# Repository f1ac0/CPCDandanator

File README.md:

# CPCDandanator
This project is a personal version of the famous "CPC Dandanator! Mini" by Dandare : http://www.dandare.es/Proyectos_Dandare/CPC_Dandanator%21_Mini.html .

Facts about this project :
- I wanted badly to try out "Sword of Ianna", so I built it on breadboard with the parts I had in stock :
- Flash ROM in DIP format,
- XC9572XL in VQ64 package (although Kicad files with VQ44 are also provided).

It ended on its own PCB with additional changes : 
- It can accommodate a card-edge connector or a pin header.
- I used a crystal-less CH340E to reduce BOM. WARNING: serial/USB communication does not work for me :( 

# Disclaimer
This is a hobbyist project, it comes with no warranty and no support. Also remember that the Amstrad machines are about 30 years old and may fail because of such hardware expansions.

The original "CPC Dandanator! Mini" is "a Public Domain project and all code/hardware/description is free to use with no restriction whatsoever" thanks to its author.

This version is not connected to Dandare, please don't bother him with issues you might have because of it.

If you find it useful and want to reward someone : reward the original author.

# BOM
- 1x XC9572XL CPLD
- 1x DIP SST39SF040, with socket
- 1x CH340E USB-serial converter + 1x micro USB connector
- 1x 3.3v LDO, either SPX3819M5-L-3-3 or XC6206P332MR
- 2x 1uF (or more) 0805 capacitors
- 5x 100nF 0805 capacitors
- 2x 10k 0805 resistor
- 1x 50 pins card-edge connector, or pin headers + cable to match your CPC

# Making it
Components are SMD, and have thin pin pitch. You need to know what you are doing.

Check for shorts at least between 5V, 3.3V, and GND traces before applying power !

The programming port does not need to be soldered since it needs to be programmed just once : you can just hold it in place during the few seconds required for programming.

XC9572XL code is generated and built into xsvf using Xilinx ISE 14.7 IDE then iMPACT. It requires to set "Logic optimization" to "Density". "Macrocell power setting" can be "Low" an "Slew rate" to "Slow". Original xsvf file provided by the author may work but I never tried it.

There are several methods to program the CPLD. I personally use xsvfduino : https://github.com/wschutzer/xsvfduino

CH340E and USB connector are optional if you do not plan to use USB. They dit not work for me anyway.

# Using it
This part is the same as the original device. Enjoy !

If you are a linux user like me, here is a tip to use the java application on modern systems without breaking the latest openjre provided by your distro :
- get oracle jre (for example from http://download.macromedia.com/pub/coldfusion/java/java8/8u271/jre/jre-8u271-linux-x64.tar.gz) and untar it
- start the app with ```~/jre1.8.0_271/bin/java -jar dandanator-cpc-2.3.jar```

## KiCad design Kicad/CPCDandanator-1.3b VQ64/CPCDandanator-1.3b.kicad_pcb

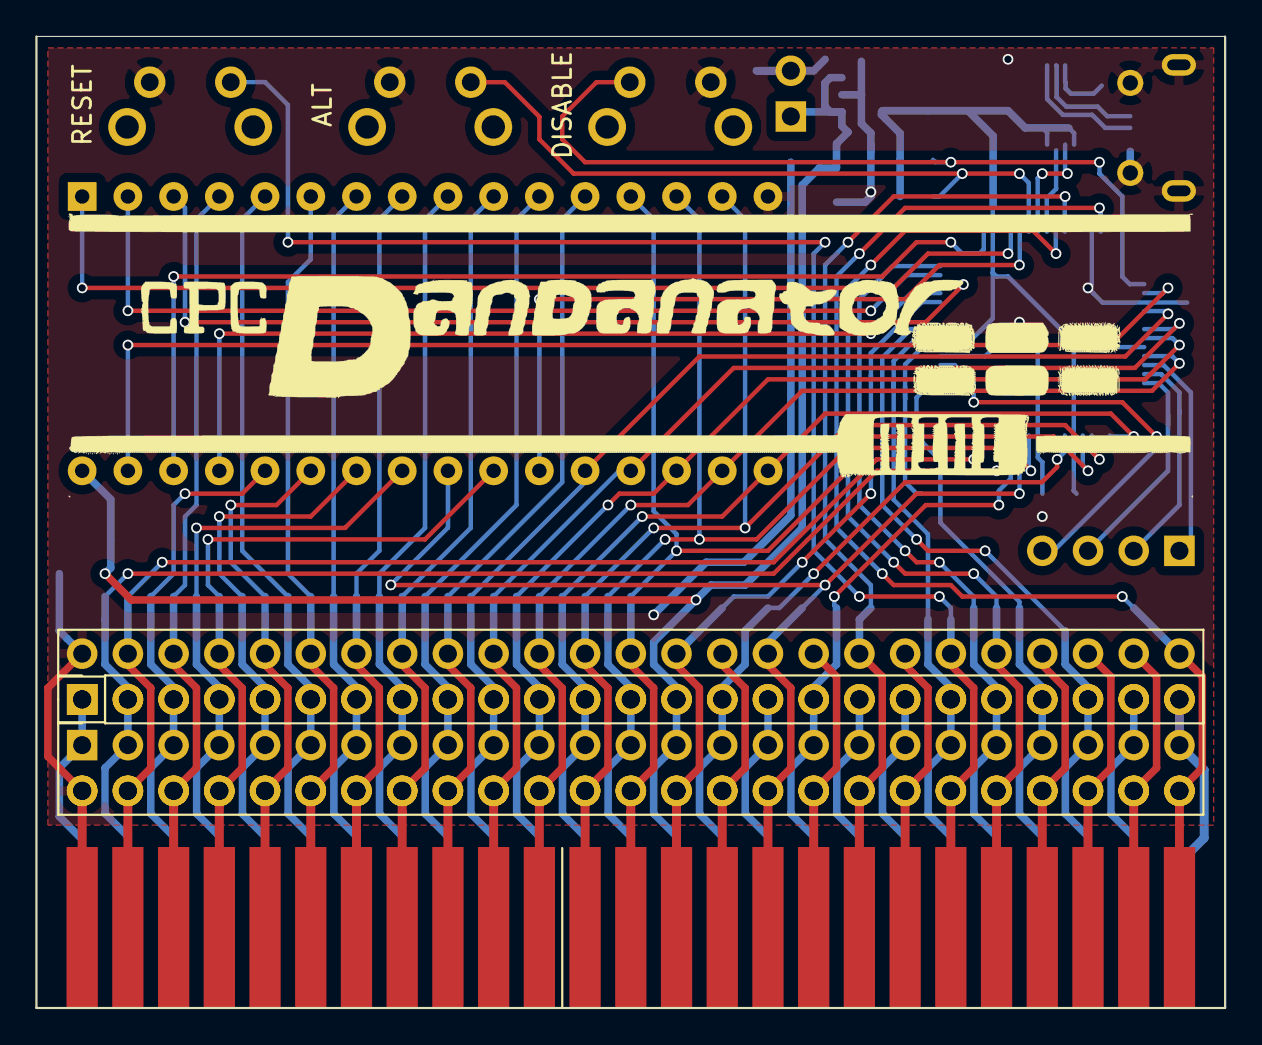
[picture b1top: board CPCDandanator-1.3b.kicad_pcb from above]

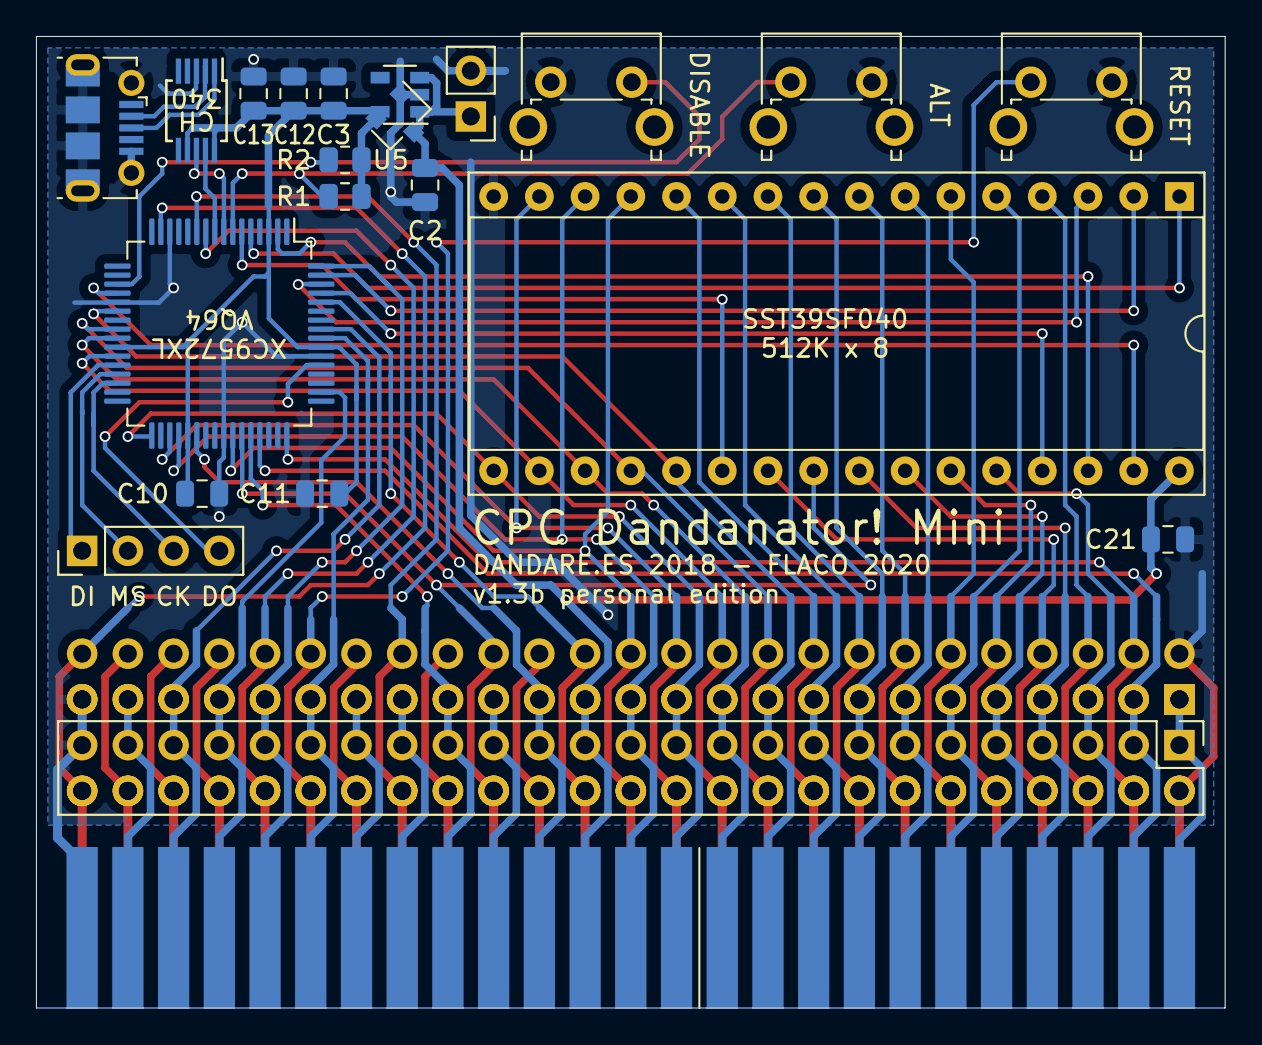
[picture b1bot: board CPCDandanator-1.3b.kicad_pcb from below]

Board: 2 copper layers, 66.0 x 54.0 mm, 25 parts (22 on the bottom side), 67 nets.

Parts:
C2, C3: 10uF; C_0805_2012Metric
C10, C11, C12, C13, C21: 100n; C_0805_2012Metric
FID1: Logo; PIC_Dandanator_FS_B
J1: TO CPC CARD EDGE; CPC_ExpansionSocket_2x25_P2.54mm_5mm
J2: TO CPC MX-4 ribbon; PinHeader_2x25_P2.54mm_Vertical
J3: POWER; PinHeader_1x02_P2.54mm_Vertical
J4: CPLD_JTAG; PinHeader_1x04_P2.54mm_Vertical
J5: USB_B_Micro; USB_Micro-B_Molex-105017-0001
J8: FROM EXPANSION; BUS_Amstrad_CPC_Expansion_2x25_2.54mm
J9: FROM EXPANSION; PinHeader_2x25_P2.54mm_Vertical
R1, R2: 10k; R_0805_2012Metric
SW1: RESET; SW_Tactile_SPST_Angled_PTS645Vx39-2LFS
SW3: ALTERNATE; SW_Tactile_SPST_Angled_PTS645Vx39-2LFS
SW4: DISABLE; SW_Tactile_SPST_Angled_PTS645Vx39-2LFS
U1: XC9572XL-VQ64; TQFP-64_10x10mm_P0.5mm
U3: 29C040; DIP-32_W15.24mm_Socket
U5: SPX3819M5-L-3-3; SOT-23-5
U12: CH340E; MSOP-10_3x3mm_P0.5mm
U15: XC6206PxxxMR; SOT-23

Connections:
+3V3: C3.1, C10.1, C11.1, C12.1, C13.1, R1.1, R2.1, U1.3, U1.26, U1.37, U1.55, U5.5, U12.7, U12.10, U15.2
+5V: C2.1, C21.1, J1.27, J2.27, J3.1, J8.27, J9.27, U3.32, U5.1, U5.3, U15.3
/A0: J1.18, J2.18, J8.18, J9.18, U3.12
/A1: J1.17, J2.17, J8.17, J9.17, U3.11
/A2: J1.16, J2.16, J8.16, J9.16, U3.10
/A3: J1.15, J2.15, J8.15, J9.15, U3.9
/A4: J1.14, J2.14, J8.14, J9.14, U3.8
/A5: J1.13, J2.13, J8.13, J9.13, U3.7
/A6: J1.12, J2.12, J8.12, J9.12, U3.6
/A7: J1.11, J2.11, J8.11, J9.11, U3.5
/A8: J1.10, J2.10, J8.10, J9.10, U3.27
/A9: J1.9, J2.9, J8.9, J9.9, U3.26
/A10: J1.8, J2.8, J8.8, J9.8, U3.23
/A11: J1.7, J2.7, J8.7, J9.7, U3.25
/A12: J1.6, J2.6, J8.6, J9.6, U3.4
/A13: J1.5, J2.5, J8.5, J9.5, U3.28
/A14: J1.4, J2.4, J8.4, J9.4, U1.48
/A15: J1.3, J2.3, J8.3, J9.3, U1.45
/BRST: J1.40, J2.40, J8.40, J9.40, SW1.1
/BUSAK: J1.38, J2.38, J8.38, J9.38
/BUSRQ: J1.37, J2.37, J8.37, J9.37
/BUTTON: R1.2, SW3.1, U1.7
/BUTTON2: R2.2, SW4.2, U1.19
/CLK4: J1.50, J2.50, J8.50, J9.50, U1.15
/CURSOR: J1.46, J2.46, J8.46, J9.46
/D0: J1.26, J2.26, J8.26, J9.26, U1.42, U3.13
/D1: J1.25, J2.25, J8.25, J9.25, U1.36, U3.14
/D2: J1.24, J2.24, J8.24, J9.24, U1.35, U3.15
/D3: J1.23, J2.23, J8.23, J9.23, U1.33, U3.17
/D4: J1.22, J2.22, J8.22, J9.22, U1.27, U3.18
/D5: J1.21, J2.21, J8.21, J9.21, U1.25, U3.19
/D6: J1.20, J2.20, J8.20, J9.20, U1.24, U3.20
/D7: J1.19, J2.19, J8.19, J9.19, U1.22, U3.21
/D+: J5.3, U12.1
/D-: J5.2, U12.2
/EXP: J1.48, J2.48, J8.48, J9.48
/HALT: J1.34, J2.34, J8.34, J9.34
/INT: J1.35, J2.35, J8.35, J9.35
/IORQ: J1.31, J2.31, J8.31, J9.31
/LPEN: J1.47, J2.47, J8.47, J9.47
/M1: J1.29, J2.29, J8.29, J9.29, U1.38
/MREQ: J1.28, J2.28, J8.28, J9.28, U1.60
/NMI: J1.36, J2.36, J8.36, J9.36, U1.11
/RAMDIS: J1.45, J2.45, J8.45, J9.45, U1.57
/RAMRD: J1.44, J2.44, J8.44, J9.44
/RD: J1.32, J2.32, J8.32, J9.32, U1.43, U3.24
/READY: J1.39, J2.39, J8.39, J9.39, U1.56
/RESET: J1.41, J2.41, J8.41, J9.41, U1.64
/RFSH: J1.30, J2.30, J8.30, J9.30
/ROMA14: U1.61, U3.29
/ROMA15: U1.62, U3.3
/ROMA16: U1.63, U3.2
/ROMA17: U1.2, U3.30
/ROMA18: U1.5, U3.1
/ROMCE: U1.6, U3.22
/ROMDIS: J1.43, J2.43, J8.43, J9.43, U1.50
/ROMEN: J1.42, J2.42, J8.42, J9.42, U1.10
/ROMWE: U1.20, U3.31
/RXD: U1.9, U12.9
/SOUND: J1.1, J2.1, J8.1, J9.1
/TCK: J4.3, U1.30
/TDI: J4.1, U1.28
/TDO: J4.4, U1.53
/TMS: J4.2, U1.29
/TXD: U1.8, U12.8
/WR: J1.33, J2.33, J8.33, J9.33, U1.44
GND: C2.2, C3.2, C10.2, C11.2, C12.2, C13.2, C21.2, J1.2, J1.49, J2.2, J2.49, J3.2, J5.5, J5.6, J8.2, J8.49, J9.2, J9.49, SW1.2, SW3.2, SW4.1, U1.14, U1.21, U1.41, U1.54, U3.16, U5.2, U12.3, U15.1

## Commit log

2021-01-19 Respository init with KiCAD files, CPLD and Readme
2022-02-15 Photo and README

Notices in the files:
Kicad/CPCDandanator-1.3b VQ64/CPCDandanator-1.3b.kicad_pcb:
FLACO 2019-2020, licence of this PCB is CC-BY-NC-SA
